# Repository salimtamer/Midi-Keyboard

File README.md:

EC11 Rotary Encoders
SK6812 MINI-E Neopixels
Bourns Slide Potentiometers
Kailh Choc Low-Profile Switches
Any other components you want, but I won't walk you through wiring them
And then your actual MIDI keys will use capacitive touch which just uses exposed copper on the PCB which uses the electrical field from your body to detect presses!

https://lapse.hackclub.com/timelapse/9ajmjLv8etyx

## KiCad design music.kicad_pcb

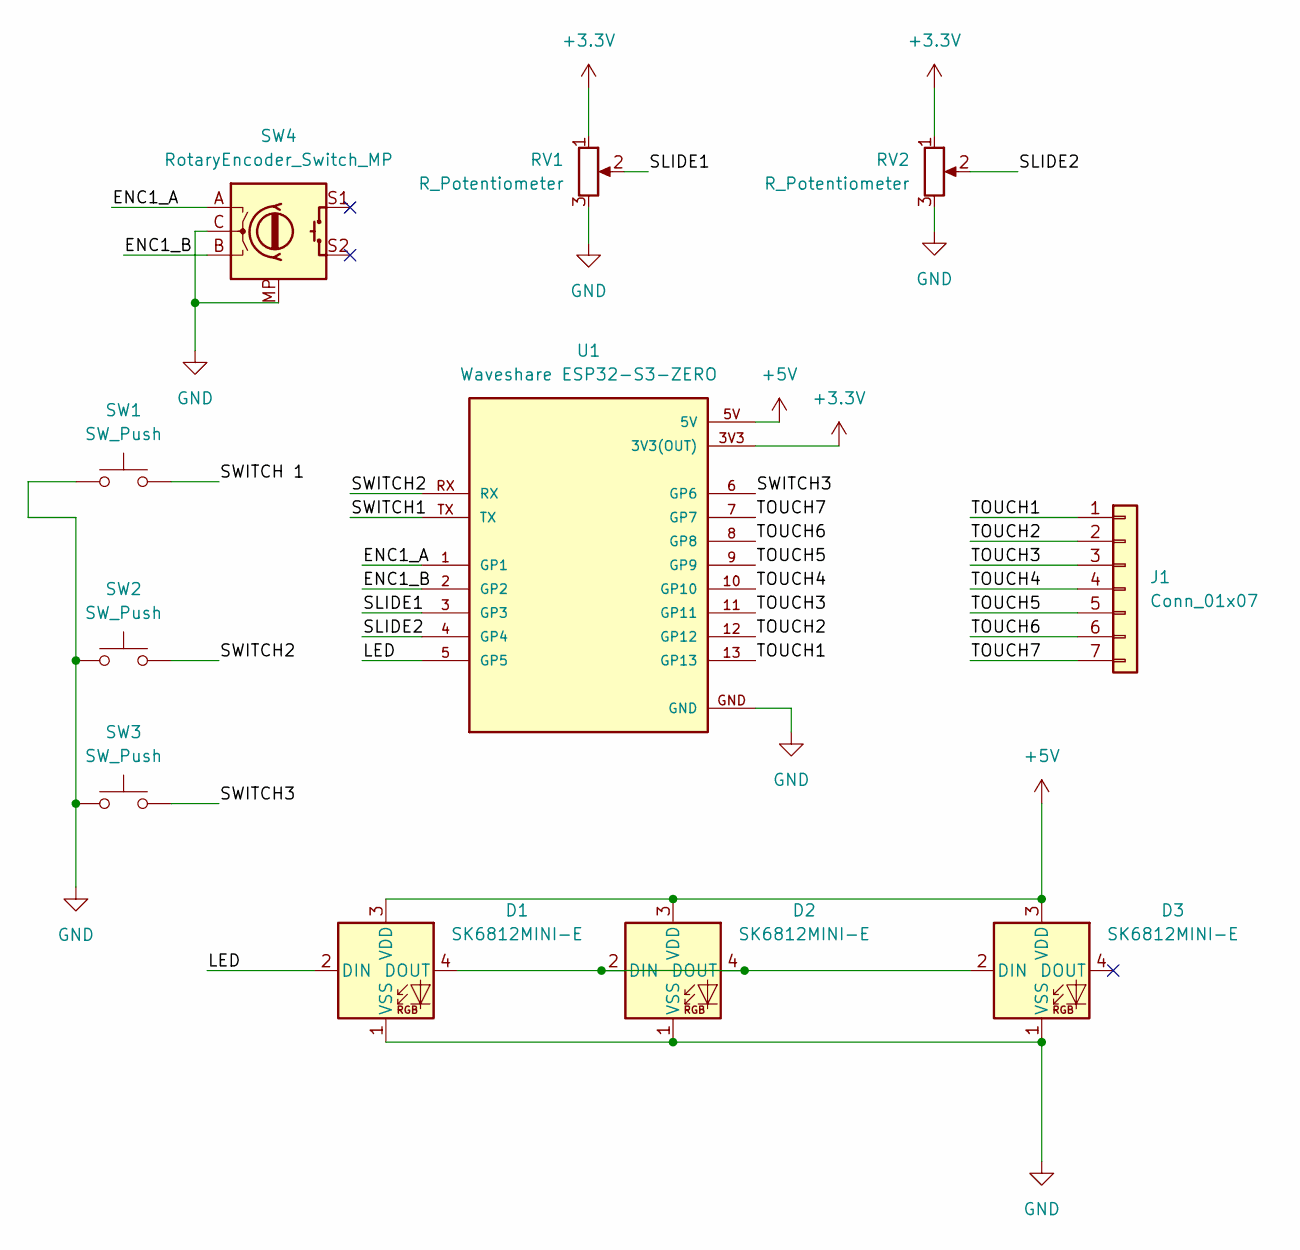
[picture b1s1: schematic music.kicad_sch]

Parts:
D1, D2, D3: SK6812MINI-E; LED_SK6812MINI-E_3.2x2.8mm_P1.5mm_ReverseMount
J1: Conn_01x07; Capacitive Keys2
RV1, RV2: R_Potentiometer; Potentiometer_Bourns_PTA1543_Single_Slide
SW1, SW2, SW3: SW_Push; Kailh Choc Low-Profile Switches
SW4: RotaryEncoder_Switch_MP; RotaryEncoder_Alps_EC11E-Switch_Vertical_H20mm
U1: Waveshare ESP32-S3-ZERO; Waveshare ESP32-S3-Zero; PARTREV NA

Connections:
+3.3V: RV1.1, RV2.1, U1.3V3 (3V3(OUT))
+5V: D1.3 (VDD), D2.3 (VDD), D3.3 (VDD), U1.5V
/ENC1_A: SW4.A, U1.1 (GP1)
/ENC1_B: SW4.B, U1.2 (GP2)
/LED: D1.2 (DIN), U1.5 (GP5)
/SLIDE1: RV1.2, U1.3 (GP3)
/SLIDE2: RV2.2, U1.4 (GP4)
/SWITCH1: U1.TX
/SWITCH2: SW2.2, U1.RX
/SWITCH3: SW3.2, U1.6 (GP6)
/SWITCH 1: SW1.2
/TOUCH1: J1.1, U1.13 (GP13)
/TOUCH2: J1.2, U1.12 (GP12)
/TOUCH3: J1.3, U1.11 (GP11)
/TOUCH4: J1.4, U1.10 (GP10)
/TOUCH5: J1.5, U1.9 (GP9)
/TOUCH6: J1.6, U1.8 (GP8)
/TOUCH7: J1.7, U1.7 (GP7)
GND: D1.1 (VSS), D2.1 (VSS), D3.1 (VSS), RV1.3, RV2.3, SW1.1, SW2.1, SW3.1, SW4.C, SW4.MP, U1.GND
unnamed: D1.4 (DOUT), D2.2 (DIN), D2.4 (DOUT), D3.2 (DIN)

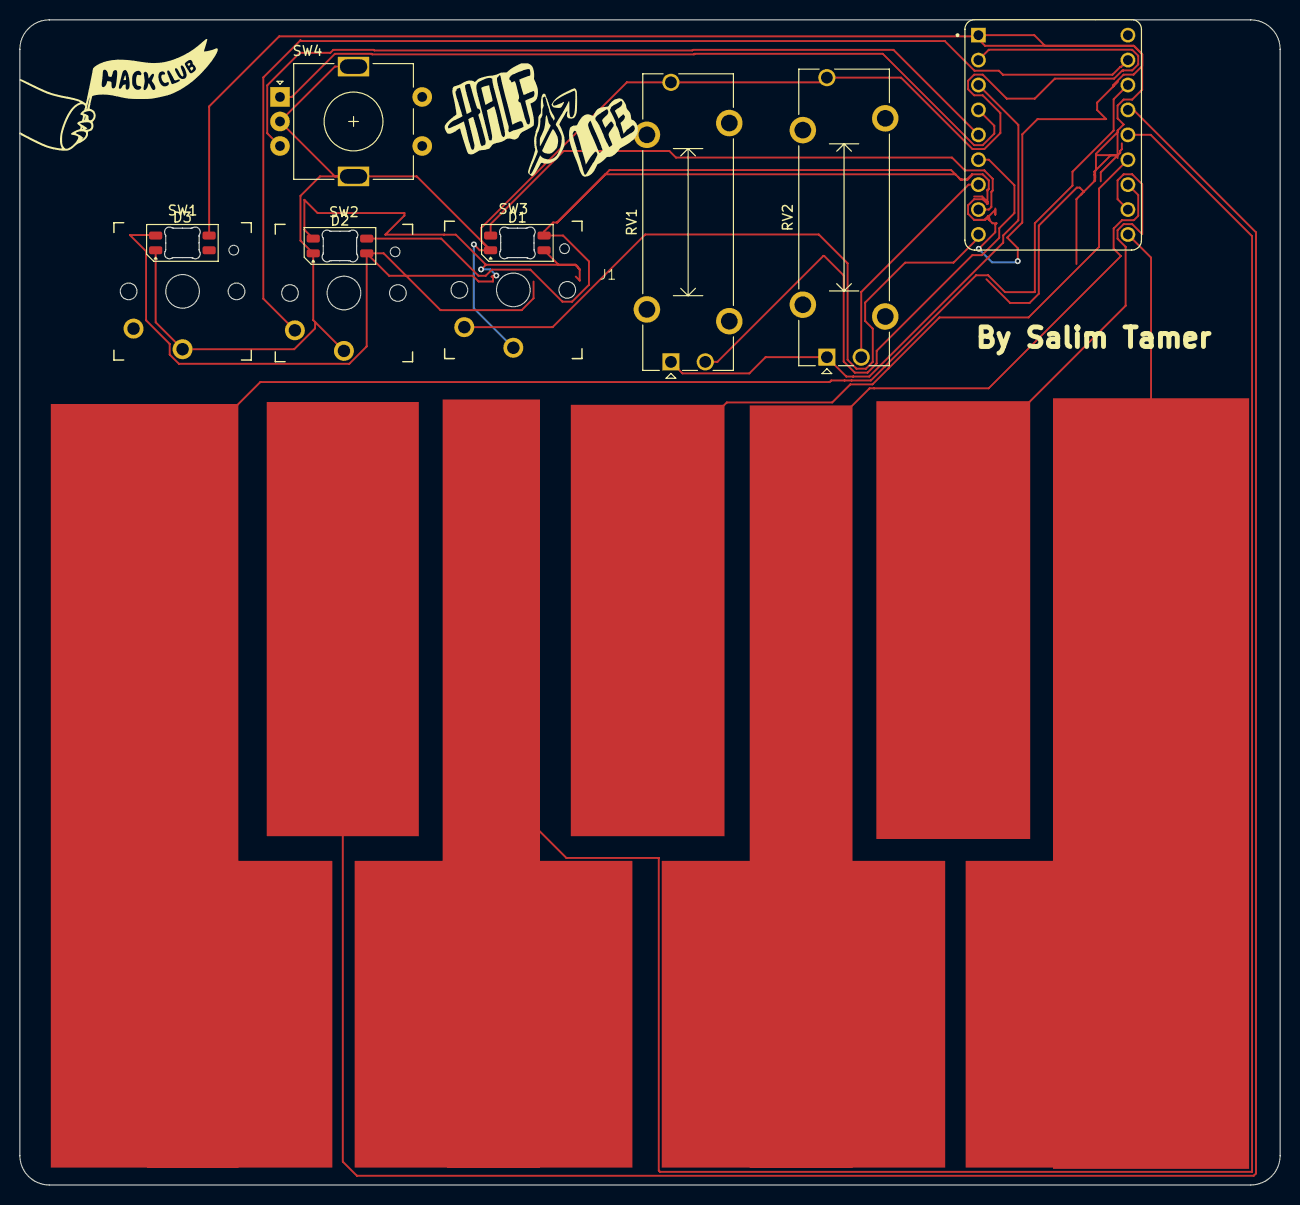
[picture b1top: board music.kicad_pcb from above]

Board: 2 copper layers, 128.5 x 118.8 mm, 11 parts (0 on the bottom side), 18 nets.

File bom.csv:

Designator,Footprint,Quantity,Value,LCSC Part #
"D1, D2, D3",LED_SK6812MINI-E_3.2x2.8mm_P1.5mm_ReverseMount,3,SK6812MINI-E,
J1,Capacitive Keys2,1,Conn_01x07,
"RV1, RV2",Potentiometer_Bourns_PTA1543_Single_Slide,2,R_Potentiometer,
"SW1, SW2, SW3",Kailh Choc Low-Profile Switches,3,SW_Push,
SW4,RotaryEncoder_Alps_EC11E-Switch_Vertical_H20mm,1,RotaryEncoder_Switch_MP,
U1,Waveshare ESP32-S3-Zero,1,Waveshare ESP32-S3-ZERO,
